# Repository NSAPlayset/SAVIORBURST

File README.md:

SAVIORBURST

A tool for building SVF files from OpenOCD logs.

----------

Before building OpenOCD, the following patches need to be applied to OpenOCD 0.9.0 
in order to support SVF generation: jtag-verbose.patch and ftdi-jtag-printing.patch 
(if using an FTDI based JTAG adapter).

Additionally, to prevent data from being truncated in the log file, the maximum 
length of scan chain data to be logged may need to be increased. This can be 
accomplished by running:

sed -i 's/define DEBUG_JTAG_IOZ 64/define DEBUG_JTAG_IOZ 1024/' src/jtag/jtag.h

----------

OpenOCD must be configured with verbose JTAG logging enabled. FTDI support (if 
needed) must also be explicitly enabled.

./configure --enable-verbose-jtag-io [--enable-ftdi]

----------

Once an OpenOCD log file has been created, log2svf.py can be used to convert it to
an SVF file.

----------

Mouser Cart (Untested) for SOLDERPEEK parts can be found here:

http://www.mouser.com/ProjectManager/ProjectDetail.aspx?AccessID=5cc594b9ce

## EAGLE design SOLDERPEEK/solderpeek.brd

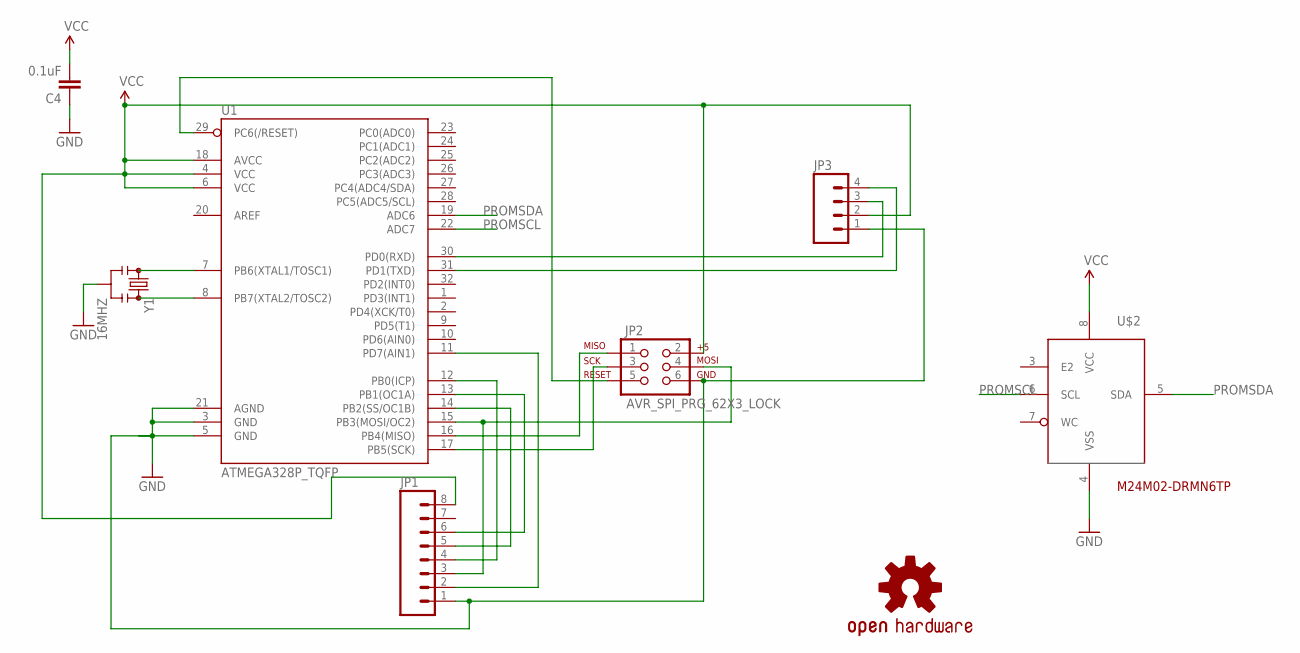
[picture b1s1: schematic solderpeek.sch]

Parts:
C4: 0.1uF; 0603-CAP
JP1: M08LOCK; 1X08_LOCK
JP2: AVR_SPI_PRG_62X3_LOCK; 2X3_LOCK
JP3: M04LOCK; 1X04_LOCK
LOGO1: OSHW-LOGOS; OSHW-LOGO-S
U1: ATMEGA328P_TQFP; TQFP32-08
U$2: M24M02-DRMN6TP; SO8
Y1: 16MHZ; RESONATOR-SMD

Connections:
GND: C4.1, JP1.1, JP2.6, JP3.1, U1.3 (GND), U1.5 (GND), U1.21 (AGND), U$2.4 (VSS), Y1.2
unnamed: U1.7 (PB6(XTAL1/TOSC1)), Y1.1
unnamed: U1.8 (PB7(XTAL2/TOSC2)), Y1.3
unnamed: JP2.1, U1.16 (PB4(MISO))
unnamed: JP1.3, JP2.4, U1.15 (PB3(MOSI/OC2))
unnamed: JP1.4, U1.12 (PB0(ICP))
unnamed: JP1.5, U1.14 (PB2(SS/OC1B))
unnamed: JP1.6, U1.13 (PB1(OC1A))
unnamed: JP1.2, U1.11 (PD7(AIN1))
unnamed: JP2.3, U1.17 (PB5(SCK))
unnamed: JP2.5, U1.29 (PC6(/RESET))
unnamed: JP3.3, U1.30 (PD0(RXD))
unnamed: JP3.4, U1.31 (PD1(TXD))
PROMSCL: U1.22 (ADC7), U$2.6 (SCL)
PROMSDA: U1.19 (ADC6), U$2.5 (SDA)
VCC: C4.2, JP1.8, JP2.2, JP3.2, U1.4 (VCC), U1.6 (VCC), U1.18 (AVCC), U$2.8 (VCC)

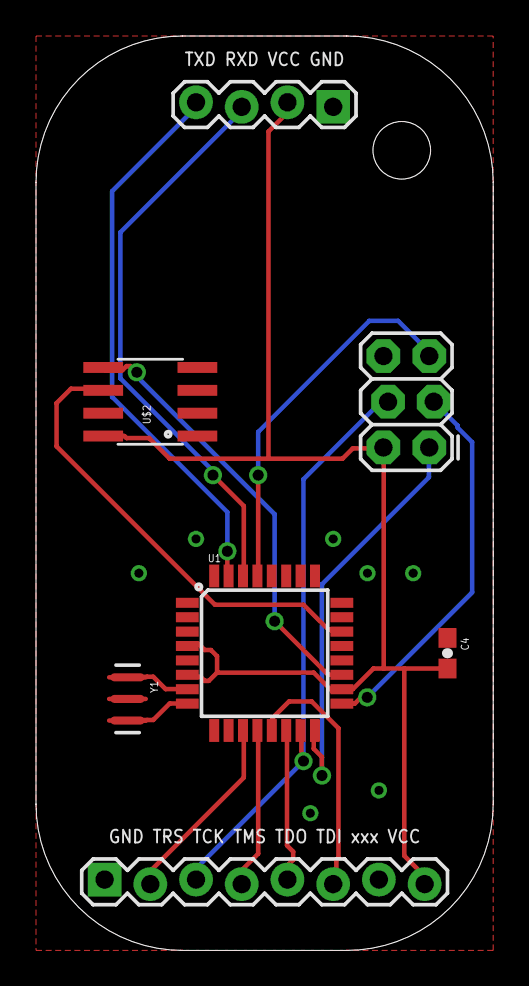
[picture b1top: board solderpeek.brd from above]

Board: 2 copper layers, 25.4 x 50.8 mm, 8 parts (1 on the bottom side), 16 nets.

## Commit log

2015-08-14 initial upload
2015-08-14 adding defcon slides
2015-08-14 adding solderpeek board files and gerbers
2015-11-23 Updating README.md to include a link to an untested Mouser cart for the parts for SOLDERPEEK

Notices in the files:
parts and their libraries:
SparkFun-Capacitors: Licensing: Creative Commons ShareAlike 4.0 International - https://creativecommons.org/licenses/by-sa/4.0
